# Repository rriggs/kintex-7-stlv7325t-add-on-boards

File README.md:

# kintex-7-stlv7325t-add-on-boards

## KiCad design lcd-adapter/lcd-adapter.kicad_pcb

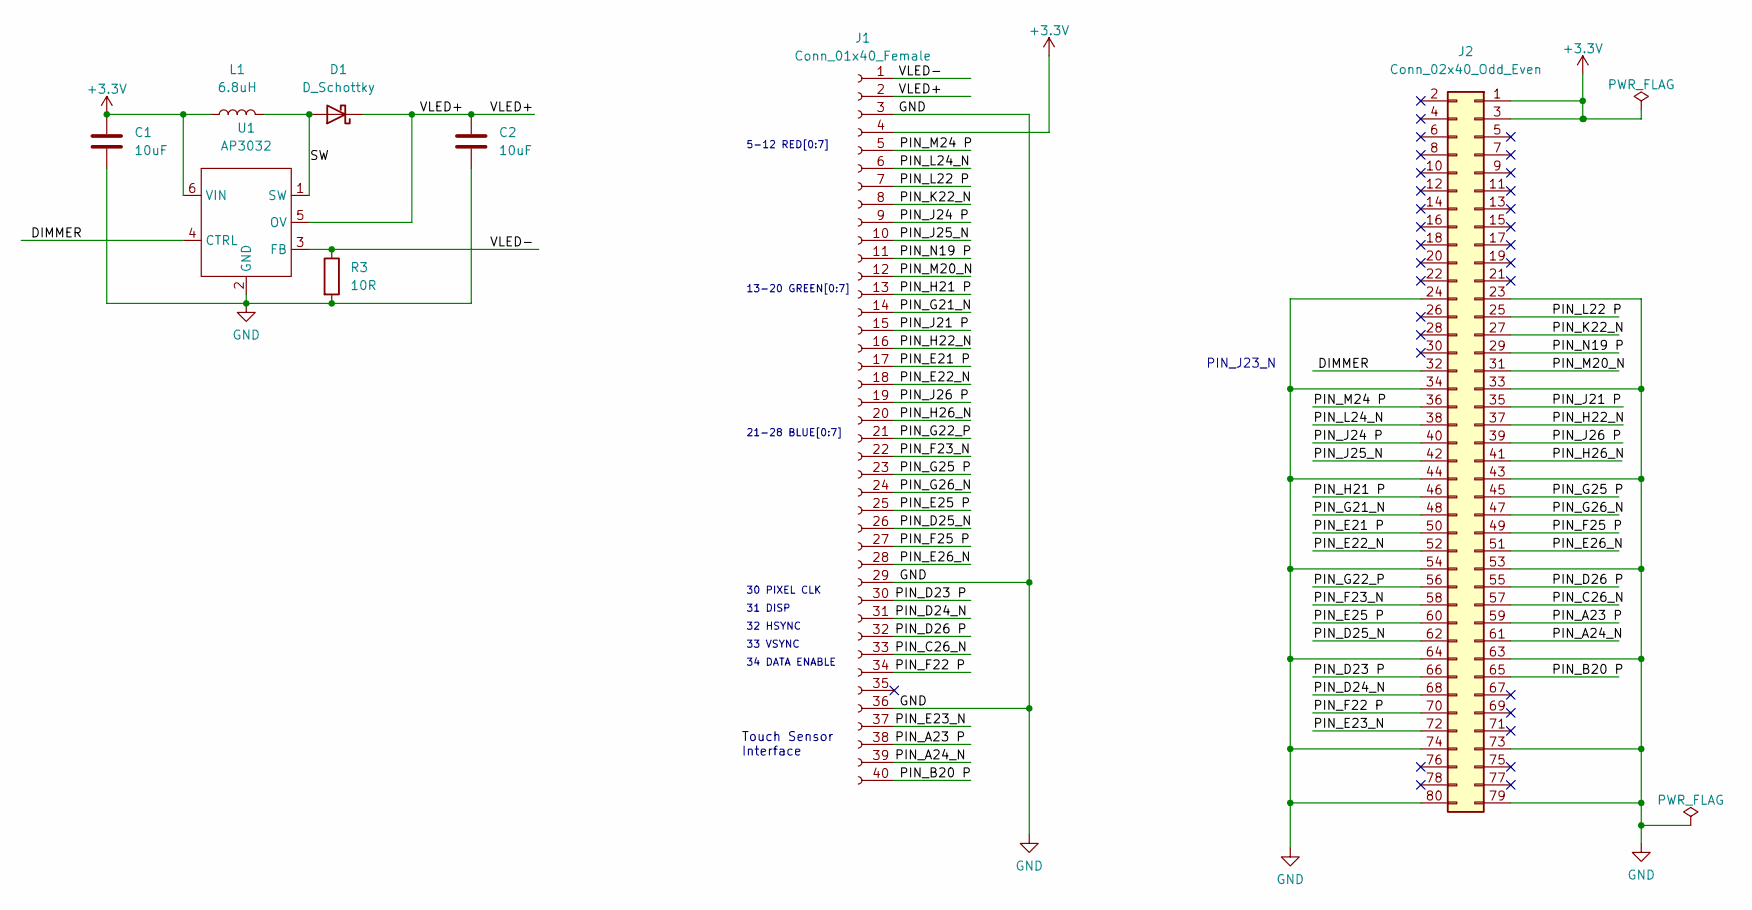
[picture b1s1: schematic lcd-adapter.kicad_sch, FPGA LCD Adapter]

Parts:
C1, C2: 10uF; C_1206_3216Metric_Pad1.33x1.80mm_HandSolder
D1: D_Schottky; D_SOD-323_HandSoldering
J1: Conn_01x40_Female; Hirose_FH12-40S-0.5SH_1x40-1MP_P0.50mm_Horizontal
J2: Conn_02x40_Odd_Even; TE_5-5179180-3
L1: 6.8uH; L_Taiyo-Yuden_NR-30xx_HandSoldering
R3: 10R; R_0603_1608Metric_Pad0.98x0.95mm_HandSolder
U1: AP3032; SOT-23-6

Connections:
+3.3V: C1.1, J1.4, J2.1, J2.3, L1.1, U1.6 (VIN)
/DIMMER: J2.32, U1.4 (CTRL)
/PIN_A23 P: J1.38, J2.59
/PIN_A24_N: J1.39, J2.61
/PIN_B20 P: J1.40, J2.65
/PIN_C26_N: J1.33, J2.57
/PIN_D23 P: J1.30, J2.66
/PIN_D24_N: J1.31, J2.68
/PIN_D25_N: J1.26, J2.62
/PIN_D26 P: J1.32, J2.55
/PIN_E21 P: J1.17, J2.50
/PIN_E22_N: J1.18, J2.52
/PIN_E23_N: J1.37, J2.72
/PIN_E25 P: J1.25, J2.60
/PIN_E26_N: J1.28, J2.51
/PIN_F22 P: J1.34, J2.70
/PIN_F23_N: J1.22, J2.58
/PIN_F25 P: J1.27, J2.49
/PIN_G21_N: J1.14, J2.48
/PIN_G22_P: J1.21, J2.56
/PIN_G25 P: J1.23, J2.45
/PIN_G26_N: J1.24, J2.47
/PIN_H21 P: J1.13, J2.46
/PIN_H22_N: J1.16, J2.37
/PIN_H26_N: J1.20, J2.41
/PIN_J21 P: J1.15, J2.35
/PIN_J24 P: J1.9, J2.40
/PIN_J25_N: J1.10, J2.42
/PIN_J26 P: J1.19, J2.39
/PIN_K22_N: J1.8, J2.27
/PIN_L22 P: J1.7, J2.25
/PIN_L24_N: J1.6, J2.38
/PIN_M20_N: J1.12, J2.31
/PIN_M24 P: J1.5, J2.36
/PIN_N19 P: J1.11, J2.29
/SW: D1.2 (A), L1.2, U1.1 (SW)
/VLED+: C2.1, D1.1 (K), J1.2, U1.5 (OV)
/VLED-: J1.1, R3.1, U1.3 (FB)
GND: C1.2, C2.2, J1.3, J1.29, J1.36, J2.23, J2.24, J2.33, J2.34, J2.43, J2.44, J2.53, J2.54, J2.63, J2.64, J2.73, J2.74, J2.79, J2.80, R3.2, U1.2 (GND)

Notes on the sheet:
13-20 GREEN[0:7]
31 DISP
33 VSYNC
34 DATA ENABLE
5-12 RED[0:7]
Touch Sensor Interface
30 PIXEL CLK
21-28 BLUE[0:7]
PIN_J23_N
32 HSYNC

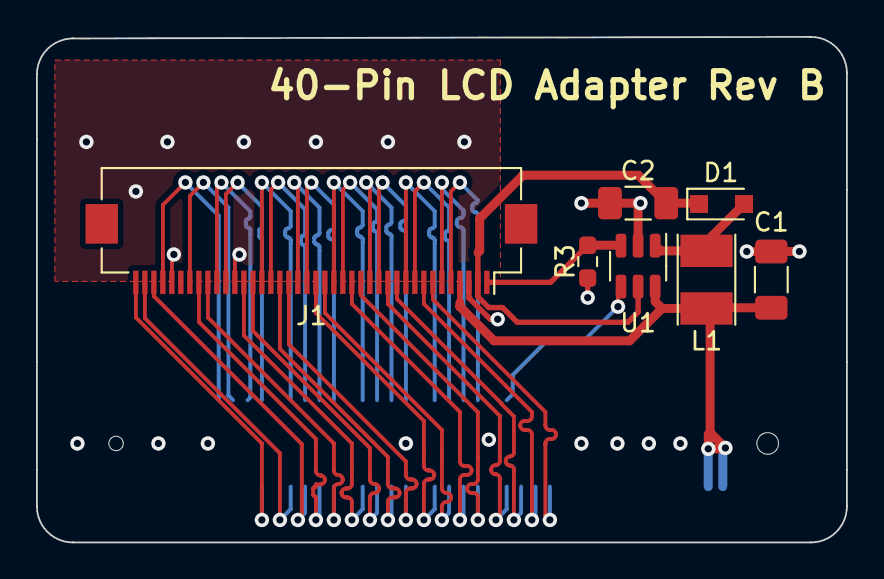
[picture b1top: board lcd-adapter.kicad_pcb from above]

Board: 4 copper layers, 45.0 x 28.1 mm, 8 parts (1 on the bottom side), 39 nets.

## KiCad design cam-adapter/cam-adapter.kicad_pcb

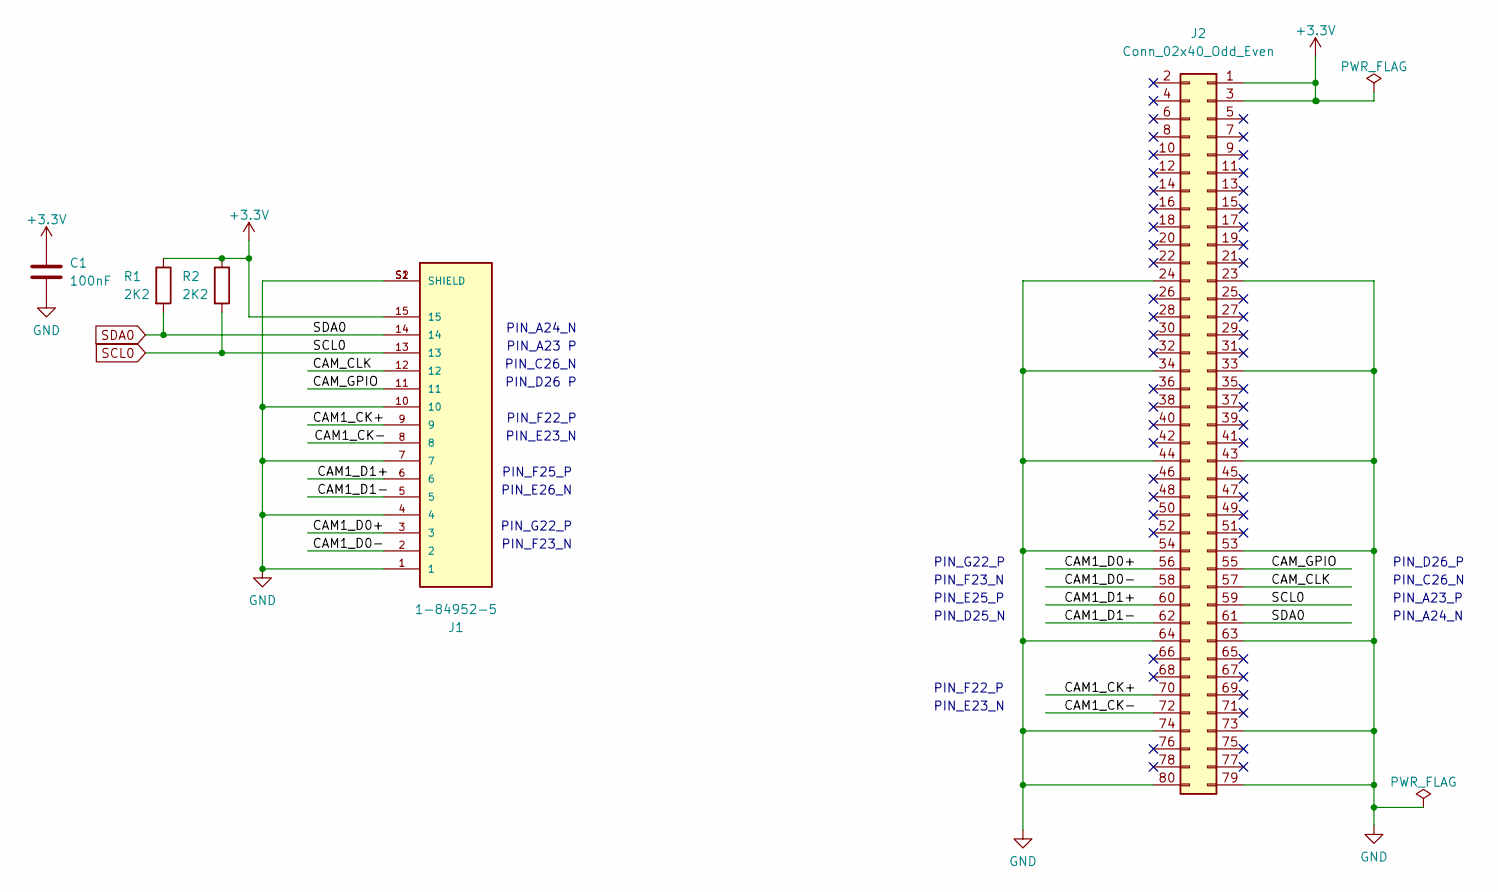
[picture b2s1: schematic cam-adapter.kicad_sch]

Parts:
C1: 100nF; C_0402_1005Metric_Pad0.74x0.62mm_HandSolder
J1: 1-84952-5; TE_1-84952-5
J2: Conn_02x40_Odd_Even; TE_5-5179180-3
R1, R2: 2K2; R_0402_1005Metric_Pad0.72x0.64mm_HandSolder

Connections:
+3.3V: C1.1, J1.15, J2.1, J2.3, R1.1, R2.1
/CAM1_CK+: J1.9, J2.70
/CAM1_CK-: J1.8, J2.72
/CAM1_D0+: J1.3, J2.56
/CAM1_D0-: J1.2, J2.58
/CAM1_D1+: J1.6, J2.60
/CAM1_D1-: J1.5, J2.62
/CAM_CLK: J1.12, J2.57
/CAM_GPIO: J1.11, J2.55
GND: C1.2, J1.1, J1.4, J1.7, J1.10, J1.S1 (SHIELD), J1.S2 (SHIELD), J2.23, J2.24, J2.33, J2.34, J2.43, J2.44, J2.53, J2.54, J2.63, J2.64, J2.73, J2.74, J2.79, J2.80
SCL0: J1.13, J2.59, R2.2
SDA0: J1.14, J2.61, R1.2

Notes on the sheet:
PIN_G22_P
PIN_E23_N
PIN_F22_P
PIN_D25_N
PIN_E26_N
PIN_F25_P
PIN_E25_P
PIN_D26 P
PIN_F23_N
PIN_C26_N
PIN_A24_N
PIN_A23 P
PIN_D26_P
PIN_A23_P

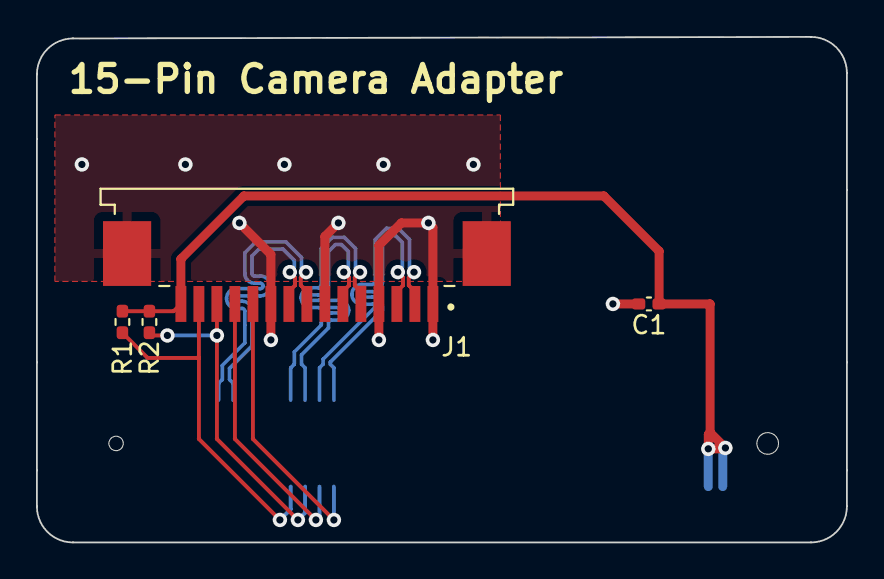
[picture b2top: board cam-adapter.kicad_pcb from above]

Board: 4 copper layers, 45.0 x 28.1 mm, 5 parts (1 on the bottom side), 12 nets.

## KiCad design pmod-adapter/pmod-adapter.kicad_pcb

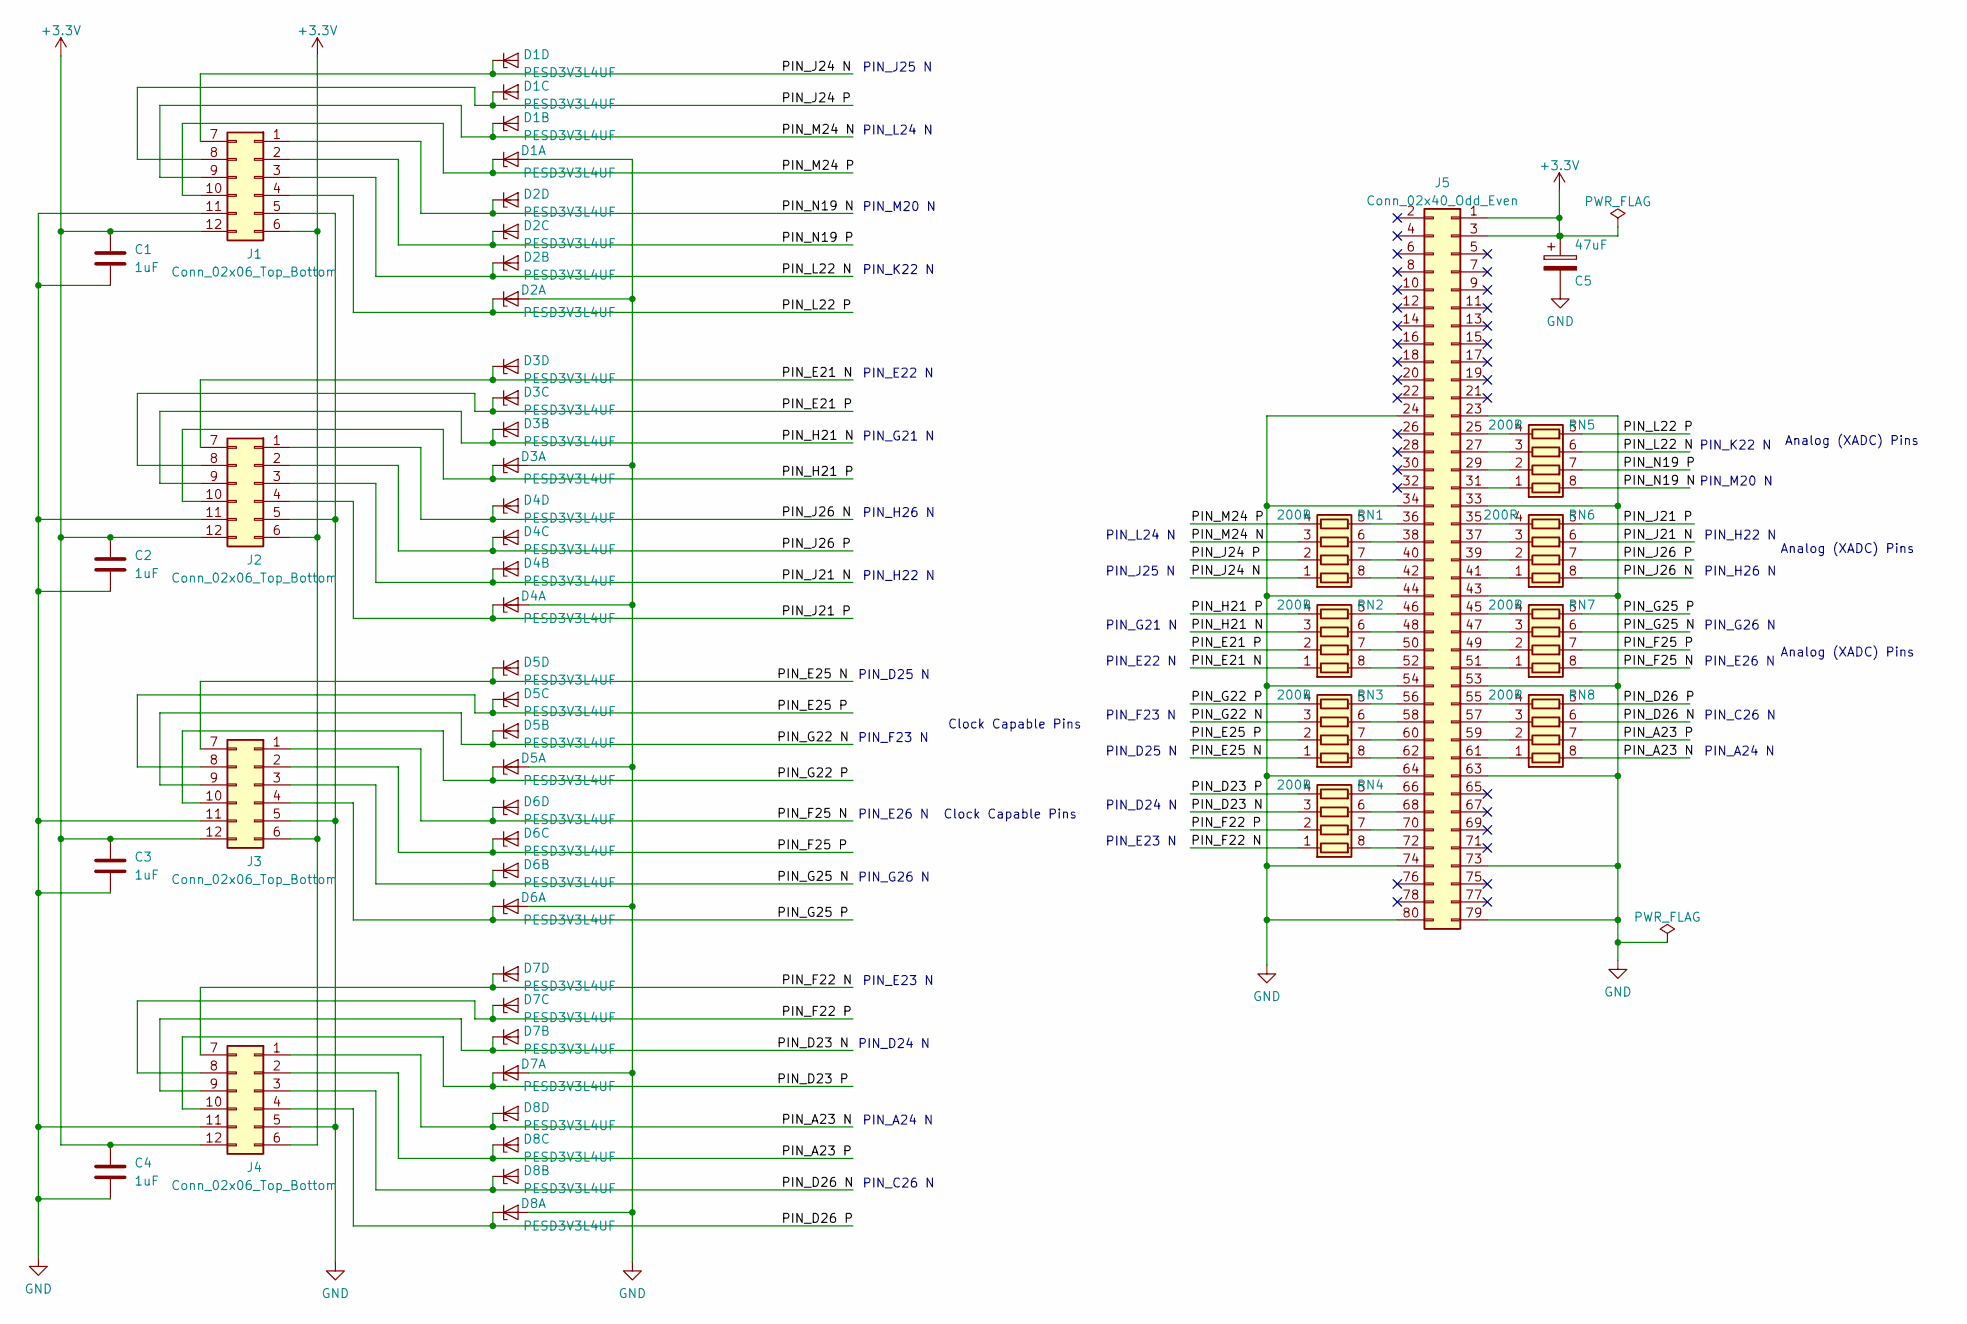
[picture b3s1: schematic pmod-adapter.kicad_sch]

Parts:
C1, C2, C3, C4: 1uF; C_0603_1608Metric
C5: 47uF; CP_Elec_5x5.4
D1, D2, D3, D4, D5, D6, D7, D8: PESD3V3L4UF; SOT1176
J1, J2, J3, J4: Conn_02x06_Top_Bottom; PMOD-connector
J5: Conn_02x40_Odd_Even; TE_5-5179180-3
RN1, RN2, RN3, RN4, RN5, RN6, RN7, RN8: 200R; R_Array_Convex_4x0402

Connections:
+3.3V: C1.1, C2.1, C3.1, C4.1, C5.1, J1.6, J1.12, J2.6, J2.12, J3.6, J3.12, J4.6, J4.12, J5.1, J5.3
/PIN_A23 N: D8.6 (K4), J4.1, RN8.8 (R1.2)
/PIN_A23 P: D8.4 (K3), J4.2, RN8.7 (R2.2)
/PIN_D23 N: D7.3 (K2), J4.9, RN4.3 (R3.1)
/PIN_D23 P: D7.1 (K1), J4.10, RN4.4 (R4.1)
/PIN_D26 N: D8.3 (K2), J4.3, RN8.6 (R3.2)
/PIN_D26 P: D8.1 (K1), J4.4, RN8.5 (R4.2)
/PIN_E21 N: D3.6 (K4), J2.7, RN2.1 (R1.1)
/PIN_E21 P: D3.4 (K3), J2.8, RN2.2 (R2.1)
/PIN_E25 N: D5.6 (K4), J3.7, RN3.1 (R1.1)
/PIN_E25 P: D5.4 (K3), J3.8, RN3.2 (R2.1)
/PIN_F22 N: D7.6 (K4), J4.7, RN4.1 (R1.1)
/PIN_F22 P: D7.4 (K3), J4.8, RN4.2 (R2.1)
/PIN_F25 N: D6.6 (K4), J3.1, RN7.8 (R1.2)
/PIN_F25 P: D6.4 (K3), J3.2, RN7.7 (R2.2)
/PIN_G22 N: D5.3 (K2), J3.9, RN3.3 (R3.1)
/PIN_G22 P: D5.1 (K1), J3.10, RN3.4 (R4.1)
/PIN_G25 N: D6.3 (K2), J3.3, RN7.6 (R3.2)
/PIN_G25 P: D6.1 (K1), J3.4, RN7.5 (R4.2)
/PIN_H21 N: D3.3 (K2), J2.9, RN2.3 (R3.1)
/PIN_H21 P: D3.1 (K1), J2.10, RN2.4 (R4.1)
/PIN_J21 N: D4.3 (K2), J2.3, RN6.6 (R3.2)
/PIN_J21 P: D4.1 (K1), J2.4, RN6.5 (R4.2)
/PIN_J24 N: D1.6 (K4), J1.7, RN1.1 (R1.1)
/PIN_J24 P: D1.4 (K3), J1.8, RN1.2 (R2.1)
/PIN_J26 N: D4.6 (K4), J2.1, RN6.8 (R1.2)
/PIN_J26 P: D4.4 (K3), J2.2, RN6.7 (R2.2)
/PIN_L22 N: D2.3 (K2), J1.3, RN5.6 (R3.2)
/PIN_L22 P: D2.1 (K1), J1.4, RN5.5 (R4.2)
/PIN_M24 N: D1.3 (K2), J1.9, RN1.3 (R3.1)
/PIN_M24 P: D1.1 (K1), J1.10, RN1.4 (R4.1)
/PIN_N19 N: D2.6 (K4), J1.1, RN5.8 (R1.2)
/PIN_N19 P: D2.4 (K3), J1.2, RN5.7 (R2.2)
GND: C1.2, C2.2, C3.2, C4.2, C5.2, D1.2 (A), D1.5 (A), D2.2 (A), D2.5 (A), D3.2 (A), D3.5 (A), D4.2 (A), D4.5 (A), D5.2 (A), D5.5 (A), D6.2 (A), D6.5 (A), D7.2 (A), D7.5 (A), D8.2 (A), D8.5 (A), J1.5, J1.11, J2.5, J2.11, J3.5, J3.11, J4.5, J4.11, J5.23, J5.24, J5.33, J5.34, J5.43, J5.44, J5.53, J5.54, J5.63, J5.64, J5.73, J5.74, J5.79, J5.80
unnamed: J5.25, RN5.4 (R4.1)
unnamed: J5.27, RN5.3 (R3.1)
unnamed: J5.29, RN5.2 (R2.1)
unnamed: J5.31, RN5.1 (R1.1)
unnamed: J5.35, RN6.4 (R4.1)
unnamed: J5.36, RN1.5 (R4.2)
unnamed: J5.37, RN6.3 (R3.1)
unnamed: J5.38, RN1.6 (R3.2)
unnamed: J5.39, RN6.2 (R2.1)
unnamed: J5.40, RN1.7 (R2.2)
unnamed: J5.41, RN6.1 (R1.1)
unnamed: J5.42, RN1.8 (R1.2)
unnamed: J5.45, RN7.4 (R4.1)
unnamed: J5.46, RN2.5 (R4.2)
unnamed: J5.47, RN7.3 (R3.1)
unnamed: J5.48, RN2.6 (R3.2)
unnamed: J5.49, RN7.2 (R2.1)
unnamed: J5.50, RN2.7 (R2.2)
unnamed: J5.51, RN7.1 (R1.1)
unnamed: J5.52, RN2.8 (R1.2)
unnamed: J5.55, RN8.4 (R4.1)
unnamed: J5.56, RN3.5 (R4.2)
unnamed: J5.57, RN8.3 (R3.1)
unnamed: J5.58, RN3.6 (R3.2)
unnamed: J5.59, RN8.2 (R2.1)
unnamed: J5.60, RN3.7 (R2.2)
unnamed: J5.61, RN8.1 (R1.1)
unnamed: J5.62, RN3.8 (R1.2)
unnamed: J5.66, RN4.5 (R4.2)
unnamed: J5.68, RN4.6 (R3.2)
unnamed: J5.70, RN4.7 (R2.2)
unnamed: J5.72, RN4.8 (R1.2)

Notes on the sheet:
Analog (XADC) Pins
PIN_E22 N
PIN_G21 N
PIN_D24 N
PIN_C26 N
PIN_E26 N
PIN_G26 N
PIN_F23 N
PIN_J25 N
PIN_H26 N
PIN_A24 N
PIN_K22 N
Clock Capable Pins
PIN_L24 N
PIN_H22 N
PIN_E23 N
PIN_D25 N
PIN_M20 N

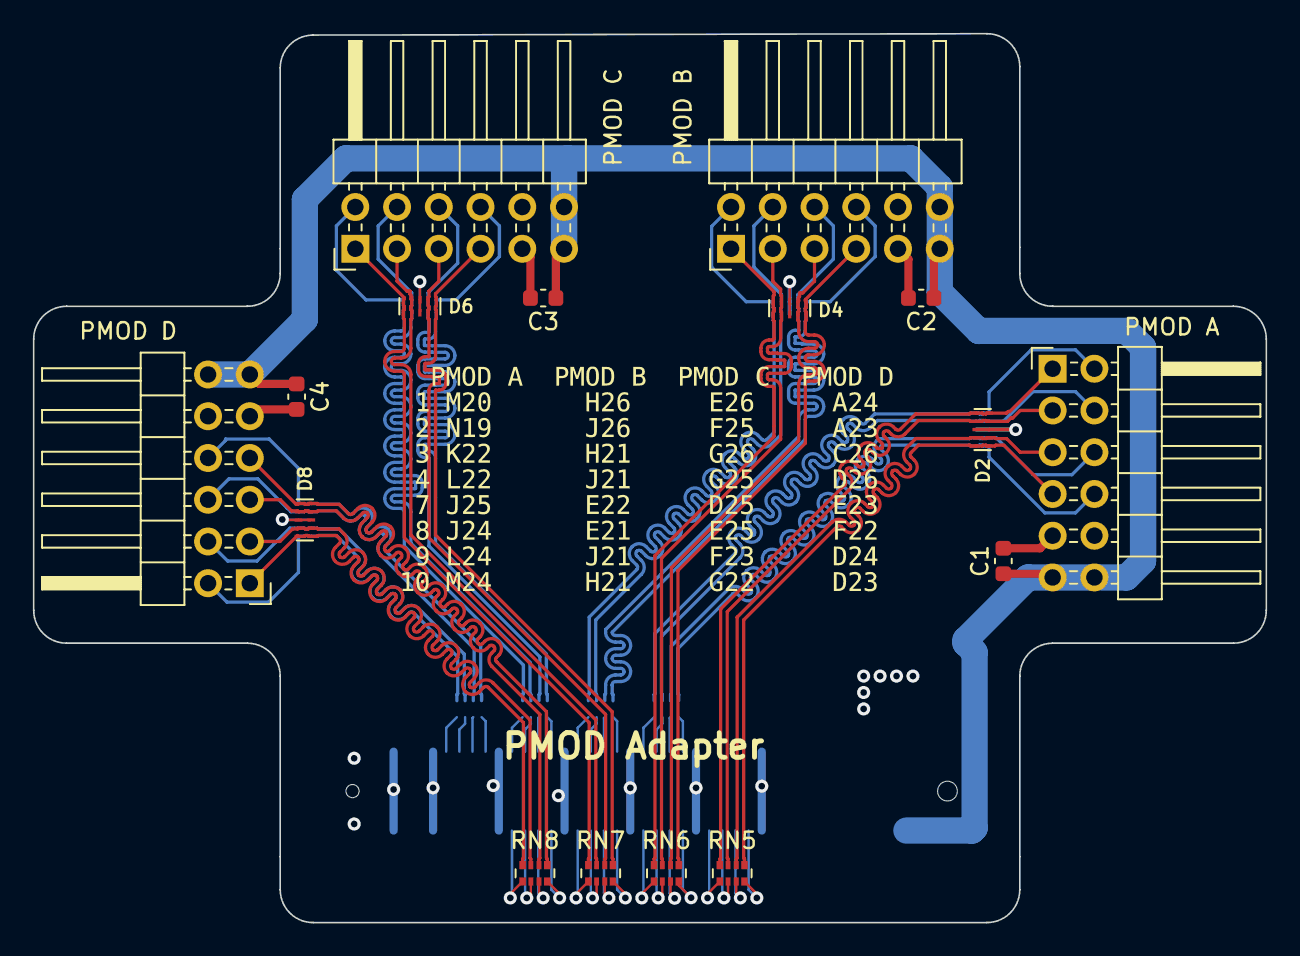
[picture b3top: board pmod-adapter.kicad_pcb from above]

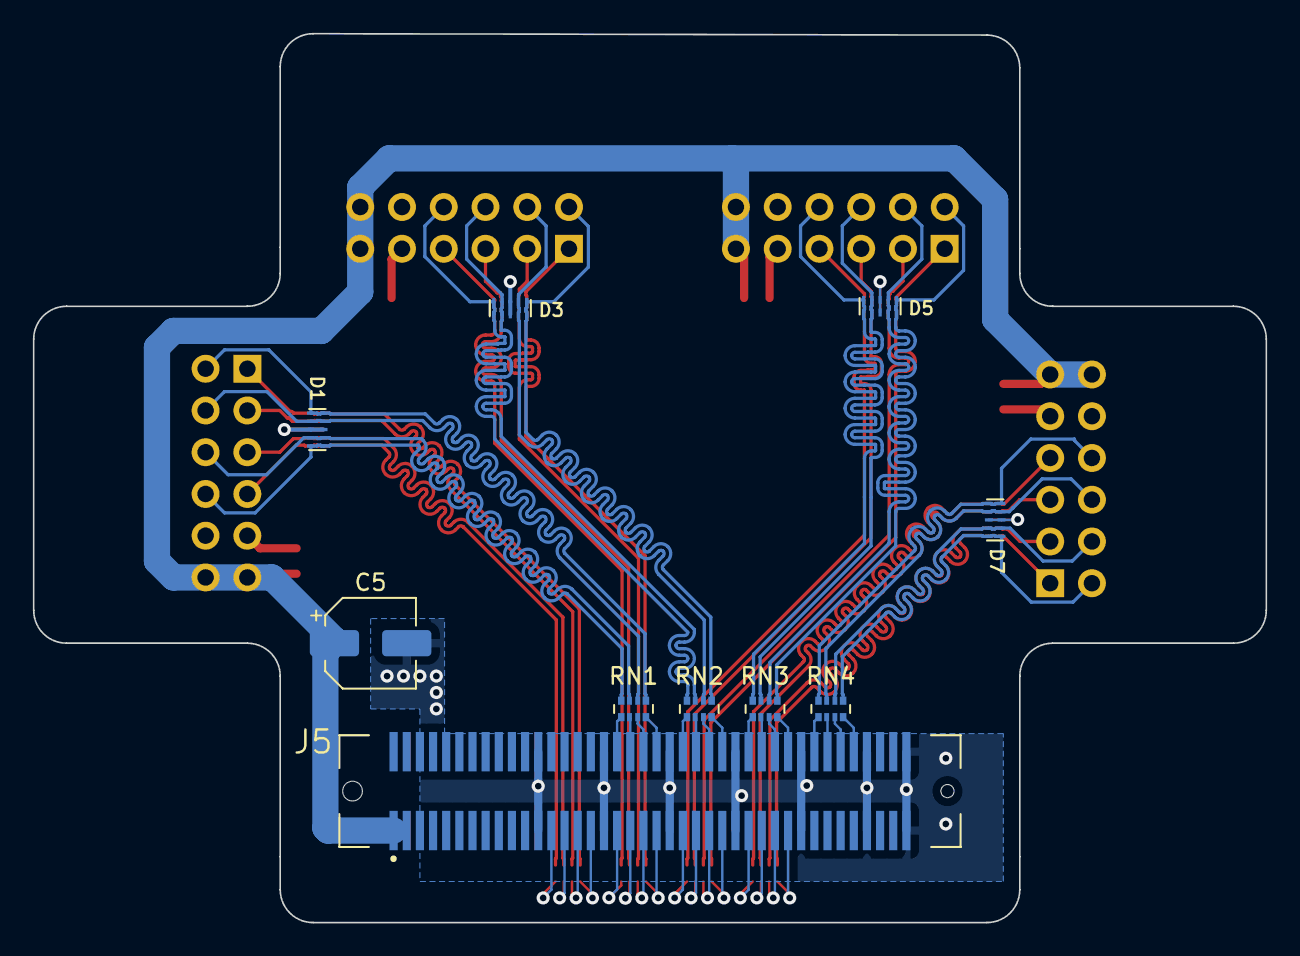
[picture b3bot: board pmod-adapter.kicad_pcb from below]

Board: 4 copper layers, 75.0 x 54.1 mm, 26 parts (10 on the bottom side), 66 nets.

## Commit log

2023-06-19 Initial commit of KiCAD files for add-on boards for the stlv7325t FPGA board.
